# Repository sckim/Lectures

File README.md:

# 🎓 임베디드 및 디지털 시스템 설계 강의 자료 (Embedded & Digital System Design)

디지털 회로의 기초 원리부터 마이크로컨트롤러를 활용한 임베디드 프로그래밍까지, 제가 담당하는 교과목의 참고자료와 실습 예제를 체계적으로 정리한 저장소입니다.

This repository systematically organizes reference materials and practical examples for courses covering everything from fundamental digital circuit principles to embedded programming using microcontrollers.

---

## 📂 저장소 구조 (Repository Structure)

```text
.
├── 📗 Digital_Logics/      # 디지털 논리회로 및 시스템 설계 (Multisim, Proteus, Quartus, Simulink)
├── 📘 MicrochipStudio/     # 마이크로컨트롤러 실습 (AVR, ATmega328P, C/Assembly CPU 동작 이해)
├── 📙 RaspberryPi/         # 임베디드 시스템 (C, 다중 스레드, GPIO, BLE IoT, Simulink)
├── 🛰️ Adafruit feather.../ # nRF52840 기반 BLE 및 시리얼 통신 예제
├── 💻 VS2019/              # C 언어 기초 및 데이터 처리 실습
├── 🔌 Schematics/          # (이동) AD2 확장 키트 → Stm32NucleoF103RB 저장소 Schematics/AD2_extension
├── 📄 References.md        # 상세 학습 참고자료 및 교재 목록
└── 📄 LICENSE              # GNU GPL v3.0
```

---

## 🎓 담당 교과목 (Courses)

### 1️⃣ [디지털논리회로 (1학기)](https://docs.google.com/document/d/1-Nbt2U4_RxmWI0knJ9PB-1zacaE4BrXKlVAKuqOXOog/edit#heading=h.l577gc53wk1r)
*   **목표**: 논리 게이트, 조합 회로 및 순차 회로의 기초 이해
*   **실습 도구별 예제**:
    *   [Multisim 예제](/Digital_Logics/Multisim/) : 기본 게이트, 가산기, 비교기, 코드 변환기, 카운터
    *   [Proteus 예제](/Digital_Logics/Proteus/) : 래치/플립플롭, 쉬프트 레지스터(74LS164/165/194/195), 멀티플렉서, 디코더
    *   [Quartus 예제](/Digital_Logics/Quartus_schematics/) : FPGA 기반 스키매틱 설계 (조합회로 → 카운터 → 상태머신 → 디지털 시계)
    *   [Simulink 예제](/Digital_Logics/Simulink/) : 모델 기반 설계 (가산기, 플립플롭, 카운터, FSM, 자판기, 신호등)

### 2️⃣ [디지털시스템설계 (2학기)](https://docs.google.com/document/d/1w0CORrWaHI_NbjOskmIDs7_7yvQ0bz3ZSNFg1BX11ck/edit#heading=h.r1hokjytc0js)
*   **목표**: VHDL/Verilog를 이용한 하드웨어 설계 언어(HDL) 기초 및 응용
*   **주요 내용**: FPGA 보드(DE1-SoC 등) 활용 실습 및 복잡한 디지털 시스템 설계
*   **참고자료**: [References.md](References.md)의 *VHDL/Verilog 문법* 항목 (HDLBits, ModelSim Testbench 튜토리얼 등)

### 3️⃣ [마이크로컨트롤러 (1학기)](https://docs.google.com/document/d/1n3KUeXxMnC6K4D472Y-YwuZHPKo5krAnx2WdAsmD2wA/edit#heading=h.g1r703qpvjvj)
*   **목표**: AVR 아키텍처 이해 및 레지스터 기반 제어 학습
*   **실습 구성**:
    *   [C/Assembly 분석](/MicrochipStudio) : Disassembler와 디버거를 통한 CPU 동작 원리 이해 (`asmStart`, `asmBlink`, `add`, `return`, `while`)
    *   [C 언어 복습](/VS2019) : 임베디드 C 기초 다지기 (구조체, 파일 입출력, 디지털 필터, 시리얼 통신)
    *   [AD2 확장 키트](https://github.com/sckim/Stm32NucleoF103RB/tree/main/Schematics/AD2_extension) : Analog Discovery 2 연동 실습 보드 (KiCad, UNO/Nucleo/Feather 지원, I2C·PWM·SPI 레벨 시프터 온보드) — 2026-10 [Stm32NucleoF103RB](https://github.com/sckim/Stm32NucleoF103RB) 저장소로 이동

### 4️⃣ [임베디드시스템 (2학기)](https://docs.google.com/document/d/1DVsG6Le9iVnEqlcv0TA36XSPXYZ1sAhT7xt2vGAz96Q/edit)
*   **목표**: 고성능 프로세서 환경에서의 임베디드 운영체제 및 응용 프로그래밍
*   **주요 플랫폼**:
    *   교재 「라즈베리파이로 배우는 임베디드 시스템」 : 원고와 장별 예제 코드는 별도 저장소(`RaspberryPi_Textbook`, 비공개)에서 관리
    *   [Raspberry Pi 실습](/RaspberryPi) : Linux 기반 C 프로그래밍, 멀티스레드(Semaphore), 성능 측정
    *   [GPIO 제어](/RaspberryPi/Pigpio) : WiringPi / pigpio 라이브러리, RTC(DS1302), I2C LCD(PCF8574)
    *   [BLE IoT 프로젝트 (TS100)](/RaspberryPi/TS100/Gitbook) : BLE 체온계 → Raspberry Pi(Python) → AWS 클라우드 연동
    *   [nRF52840 예제](/Adafruit%20feather%20nRF52840%20express) : 저전력 블루투스(BLE) 통신 및 시리얼 통신

---

## 🛠️ 개발 환경 (Development Environment)

효과적인 학습을 위해 다음 도구들을 사용합니다:

*   **IDE**:
    *   [Microchip Studio](https://www.microchip.com/en-us/tools-resources/develop/microchip-studio) (AVR/ATmega 제어)
    *   [VS Code](https://code.visualstudio.com/) + [PlatformIO](https://platformio.org/) (추천 환경)
    *   Visual Studio 2019 (C 언어 기초)
*   **Simulation**:
    *   [Multisim](https://www.ni.com/ko-kr/support/downloads/software-products/download.multisim.html)
    *   [Proteus](https://www.labcenter.com/)
    *   [MATLAB/Simulink](https://www.mathworks.com/products/simulink.html)
*   **HDL/FPGA**: [Intel Quartus Prime](https://www.intel.co.kr/content/www/kr/ko/software/programmable/quartus-prime/overview.html)
*   **PCB 설계**: [KiCad](https://www.kicad.org/) ([KiCad 라이브러리 저장소](https://github.com/sckim/KiCAD))

---

## 🚀 시작하기 (Getting Started)

1.  **저장소 복제 (Clone)**:
    ```bash
    git clone https://github.com/sckim/Lectures.git
    ```
2.  **참고자료 확인**: [References.md](References.md)에서 교재 및 온라인 강의 링크를 확인하세요.
3.  **예제 실행**: 각 폴더의 README를 참고하여 프로젝트 파일을 해당 IDE에서 열어 실행합니다.
    *   Quartus 프로젝트는 `.qpf`, Microchip Studio는 `MicrochipStudio.atsln`, Visual Studio는 `VS2019.sln`을 엽니다.
    *   빌드 산출물(`db/`, `output_files/`, `Debug/` 등)은 저장소에 포함되지 않으므로 처음 열 때 한 번 컴파일하세요.

---

## ✉️ 문의 및 피드백 (Contact & Feedback)

학습 중 궁금한 점이나 보완이 필요한 내용은 언제든지 아래로 연락 바랍니다:
*   **이메일**: sckim@hknu.ac.kr
*   **GitHub Issues**: 오류 제보나 기능 제안은 Issue를 이용해 주세요.

---

## ⚖️ 라이선스 (License)

이 저장소의 코드는 [GNU General Public License v3.0](LICENSE)을 따릅니다.

---
*지속적으로 업데이트 중입니다. 학생 여러분의 학습에 도움이 되길 바랍니다!*

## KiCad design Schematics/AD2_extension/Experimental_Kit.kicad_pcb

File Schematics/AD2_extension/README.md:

# 🔌 AD2 확장 키트 (Analog Discovery 2 Extension Kit)

Analog Discovery 2(AD2)와 마이크로컨트롤러 보드를 함께 꽂아 실습하는 확장 보드의 KiCad 프로젝트입니다.
Arduino UNO R3 호환 헤더, STM32 Nucleo Morpho 헤더(CN7/CN10), Adafruit Feather 소켓을 지원하며, 5V 주변장치(LCD, PWM)와 3.3V 주변장치(SPI)를 위한 레벨 시프터가 보드에 실장되어 있습니다.

---

## 📂 파일 구성 (Files)

| 파일 | 내용 |
| :--- | :--- |
| `Experimental_Kit.kicad_pro` | KiCad 프로젝트 파일 (이 파일을 여세요) |
| `Experimental_Kit.kicad_sch` | 회로도 |
| `Experimental_Kit.kicad_pcb` | PCB (2층, 배선 및 GND 동박 완료) |
| `AD2_extension.kicad_sym`, `sym-lib-table` | 프로젝트 심볼 라이브러리 (TXU0304PW) |
| `AD2_extension.pretty/`, `fp-lib-table` | 프로젝트 풋프린트 라이브러리 (UNO 실드 헤더, 2×19 미러 소켓) |

---

## 🧩 커넥터 (Connectors)

| 레퍼런스 | 이름 | 용도 |
| :--- | :--- | :--- |
| A1 | Arduino_UNO_R3 | Arduino UNO R3 호환 헤더 |
| J11 / J13 | CN7 / CN10 | STM32 Nucleo Morpho 헤더 |
| MS1 | Feather | Adafruit Feather 소켓 |
| J10 | AD2 | Analog Discovery 2 연결 |
| J2 | Keypad | 키패드 (전원 IOREF) |
| J3 | LCD | I2C LCD (5V, 레벨 시프트된 SDA/SCL) |
| J5 / J6 | PWM | 5V PWM 출력 (DIO3 / DIO5) |
| J14 | SPI | 3.3V SPI 장치 |
| J12 | IOREF | IOREF–3V3 연결 헤더 (아래 참고) |
| J7 / J9 | AREF / W1 | 아날로그 기준 전압 / AD2 파형 발생기 |

---

## 🔁 온보드 레벨 시프터 (On-board Level Shifters)

이전 버전은 BSS138 레벨 시프터 모듈을 헤더(J2/J4)에 꽂아 사용했으나, 현재는 보드에 직접 실장했습니다.
호스트 쪽 전압은 **IOREF**를 기준으로 하므로 5V 보드(UNO)와 3.3V 보드(Nucleo, Feather) 모두에서 규격에 맞는 신호 레벨이 나옵니다.

| 신호 | 회로 | 방향 |
| :--- | :--- | :--- |
| SDA, SCL → LCD | 2N7002 MOSFET (Q1, Q2), 호스트 쪽 풀업 4.7kΩ, 5V 쪽 풀업 10kΩ | 양방향 |
| DIO3, DIO5 → PWM | 2N7002 MOSFET (Q3, Q4), 풀업 10kΩ | IOREF → 5V |
| DIO13/11/10 → SCK/MOSI/CS | TXU0304 (U1), VCCA = IOREF, VCCB = 3.3V | 호스트 → 장치 |
| MISO ← DIO12 | TXU0304 (U1) | 장치 → 호스트 |

> ⚠️ **Feather 사용 시**: Feather에는 IOREF 핀이 없으므로 **J12(IOREF)에 점퍼를 꽂아** IOREF를 3.3V에 연결해야 레벨 시프터가 동작합니다. UNO/Nucleo 사용 시에는 점퍼를 빼 두세요.

---

## 🛠️ 여는 방법 (How to Open)

1. [KiCad](https://www.kicad.org/) 최신 버전을 설치합니다.
2. `Experimental_Kit.kicad_pro`를 엽니다. 프로젝트 라이브러리(`sym-lib-table`, `fp-lib-table`)는 자동으로 로드됩니다.
3. 추가 라이브러리는 [KiCad 라이브러리 저장소](https://github.com/sckim/KiCAD)를 참고하세요.

---

*[메인 README.md로 돌아가기](../../README.md)*

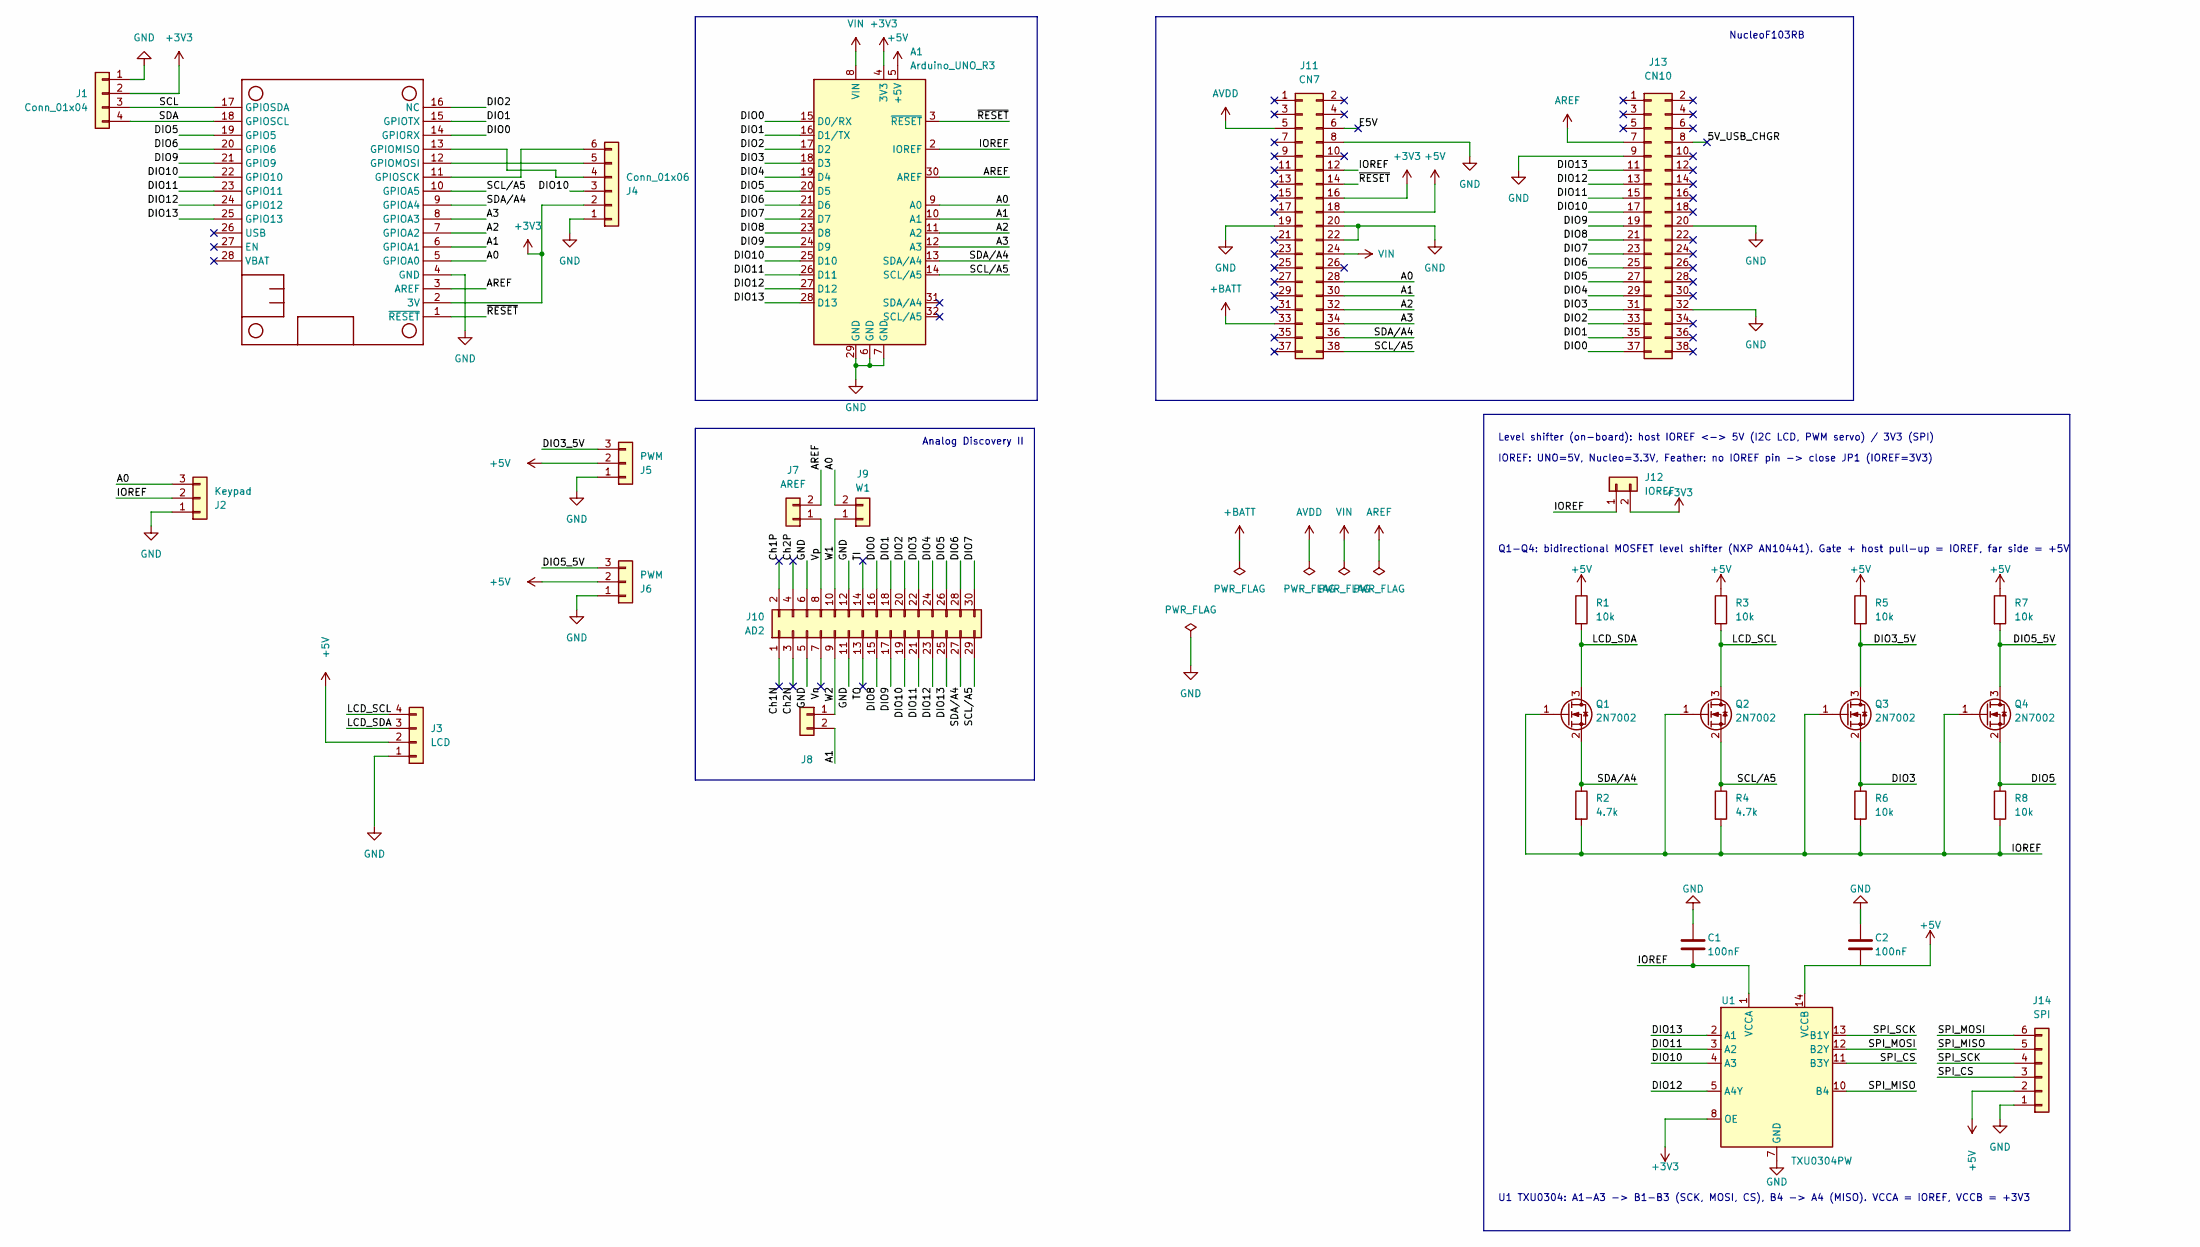
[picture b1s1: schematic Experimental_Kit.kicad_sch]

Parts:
A1: Arduino_UNO_R3; Arduino_UNO_R3_ShieldHeaders
C1, C2: 100nF; C_0805_2012Metric_Pad1.18x1.45mm_HandSolder
J1: Conn_01x04; PinHeader_1x04_P2.54mm_Vertical
J2: Keypad; PinHeader_1x03_P2.54mm_Vertical
J3: LCD; PinHeader_1x04_P2.54mm_Vertical
J4: Conn_01x06
J5, J6: PWM; PinHeader_1x03_P2.54mm_Vertical
J7: AREF; PinHeader_1x02_P2.54mm_Vertical
J8: Conn_01x02; PinHeader_1x02_P2.54mm_Vertical
J9: W1; PinHeader_1x02_P2.54mm_Vertical
J10: AD2; PinSocket_2x15_P2.54mm_Horizontal
J11: CN7; PinSocket_2x19_P2.54mm_Vertical_Mirrored
J12: IOREF; PinHeader_1x02_P2.54mm_Vertical
J13: CN10; PinSocket_2x19_P2.54mm_Vertical_Mirrored
J14: SPI; PinHeader_1x06_P2.54mm_Vertical
MS1: FEATHERWING_NODIM
Q1, Q2, Q3, Q4: 2N7002; SOT-23
R1, R3, R5, R6, R7, R8: 10k; R_0805_2012Metric_Pad1.20x1.40mm_HandSolder
R2, R4: 4.7k; R_0805_2012Metric_Pad1.20x1.40mm_HandSolder
U1: TXU0304PW; TSSOP-14_4.4x5mm_P0.65mm

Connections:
+3V3: A1.4 (3V3), J1.2, J4.2, J11.16, J12.2, MS1.2 (3V), U1.8 (OE)
+5V: A1.5 (+5V), J3.2, J5.2, J6.2, J11.18, J14.2, R1.1, R3.1, R5.1, R7.1, U1.14 (VCCB)
+BATT: J11.33
/5V_USB_CHGR: J13.8
/A0: A1.9 (A0), J2.3, J9.2, J11.28, MS1.5 (GPIOA0)
/A1: A1.10 (A1), J8.2, J11.30, MS1.6 (GPIOA1)
/A2: A1.11 (A2), J11.32, MS1.7 (GPIOA2)
/A3: A1.12 (A3), J11.34, MS1.8 (GPIOA3)
/Ch1N: J10.1
/Ch1P: J10.2
/Ch2N: J10.3
/Ch2P: J10.4
/DIO0: A1.15 (D0/RX), J10.16, J13.37, MS1.14 (GPIORX)
/DIO1: A1.16 (D1/TX), J10.18, J13.35, MS1.15 (GPIOTX)
/DIO2: A1.17 (D2), J10.20, J13.33, MS1.16 (NC)
/DIO3: A1.18 (D3), J10.22, J13.31, Q3.2 (S), R6.1
/DIO3_5V: J5.3, Q3.3 (D), R5.2
/DIO4: A1.19 (D4), J10.24, J13.29
/DIO5: A1.20 (D5), J10.26, J13.27, MS1.19 (GPIO5), Q4.2 (S), R8.1
/DIO5_5V: J6.3, Q4.3 (D), R7.2
/DIO6: A1.21 (D6), J10.28, J13.25, MS1.20 (GPIO6)
/DIO7: A1.22 (D7), J10.30, J13.23
/DIO8: A1.23 (D8), J10.15, J13.21
/DIO9: A1.24 (D9), J10.17, J13.19, MS1.21 (GPIO9)
/DIO10: A1.25 (D10), J4.3, J10.19, J13.17, MS1.22 (GPIO10), U1.4 (A3)
/DIO11: A1.26 (D11), J10.21, J13.15, MS1.23 (GPIO11), U1.3 (A2)
/DIO12: A1.27 (D12), J10.23, J13.13, MS1.24 (GPIO12), U1.5 (A4Y)
/DIO13: A1.28 (D13), J10.25, J13.11, MS1.25 (GPIO13), U1.2 (A1)
/E5V: J11.6
/IOREF: A1.2 (IOREF), C1.2, J2.2, J11.12, J12.1, Q1.1 (G), Q2.1 (G), Q3.1 (G), Q4.1 (G), R2.2, R4.2, R6.2, R8.2, U1.1 (VCCA)
/LCD_SCL: J3.4, Q2.3 (D), R3.2
/LCD_SDA: J3.3, Q1.3 (D), R1.2
/SCL: J1.3, MS1.17 (GPIOSDA)
/SCL/A5: A1.14 (SCL/A5), J10.29, J11.38, MS1.10 (GPIOA5), Q2.2 (S), R4.1
/SDA: J1.4, MS1.18 (GPIOSCL)
/SDA/A4: A1.13 (SDA/A4), J10.27, J11.36, MS1.9 (GPIOA4), Q1.2 (S), R2.1
/SPI_CS: J14.3, U1.11 (B3Y)
/SPI_MISO: J14.5, U1.10 (B4)
/SPI_MOSI: J14.6, U1.12 (B2Y)
/SPI_SCK: J14.4, U1.13 (B1Y)
/TI: J10.14
/TO: J10.13
/Vn: J10.7
/Vp: J7.1, J10.8
/W1: J9.1, J10.10
/W2: J8.1, J10.9
/~RESET: A1.3 (~RESET), J11.14, MS1.1 (~RESET)
AREF: A1.30 (AREF), J7.2, J13.7, MS1.3 (AREF)
AVDD: J11.5
GND: A1.6 (GND), A1.7 (GND), A1.29 (GND), C1.1, C2.1, J1.1, J2.1, J3.1, J4.1, J5.1, J6.1, J10.5, J10.6, J10.11, J10.12, J11.8, J11.19, J11.20, J11.22, J13.9, J13.20, J13.32, J14.1, MS1.4 (GND), U1.7 (GND)
unnamed: J4.4, MS1.13 (GPIOMISO)
unnamed: J4.5, MS1.12 (GPIOMOSI)
unnamed: J4.6, MS1.11 (GPIOSCK)
VIN: A1.8 (VIN), J11.24

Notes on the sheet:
Level shifter (on-board): host IOREF <-> 5V (I2C LCD, PWM servo) / 3V3 (SPI)
IOREF: UNO=5V, Nucleo=3.3V, Feather: no IOREF pin -> close JP1 (IOREF=3V3)
Q1-Q4: bidirectional MOSFET level shifter (NXP AN10441). Gate + host pull-up = IOREF, far side = +5V
NucleoF103RB
Analog Discovery II
U1 TXU0304: A1-A3 -> B1-B3 (SCK, MOSI, CS), B4 -> A4 (MISO). VCCA = IOREF, VCCB = +3V3

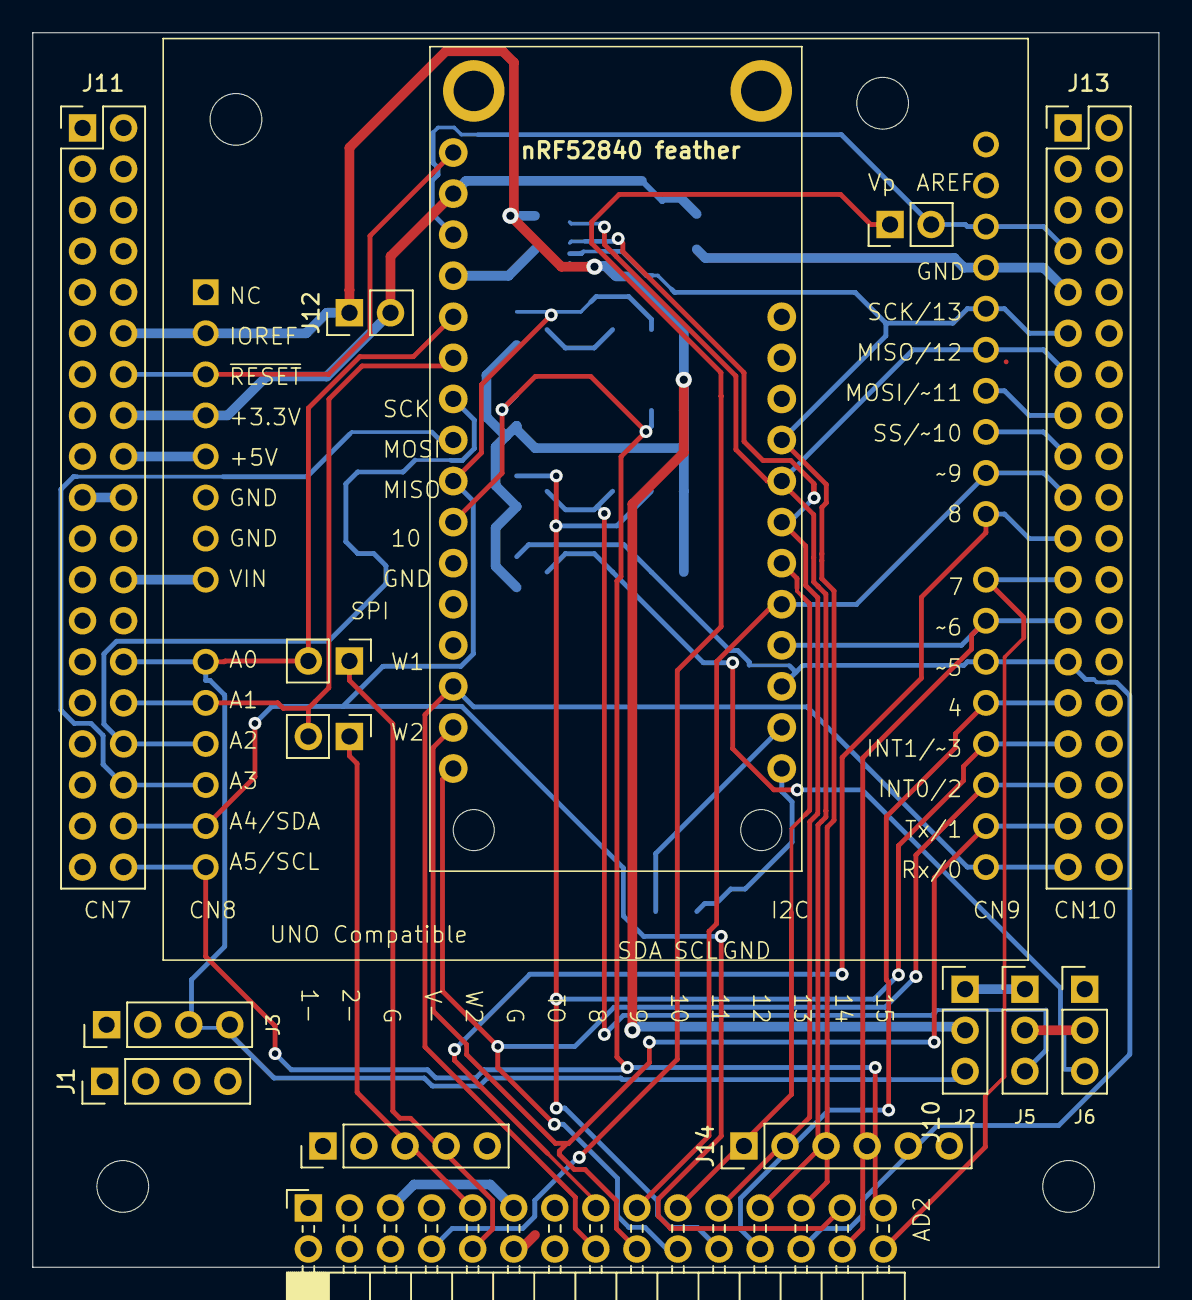
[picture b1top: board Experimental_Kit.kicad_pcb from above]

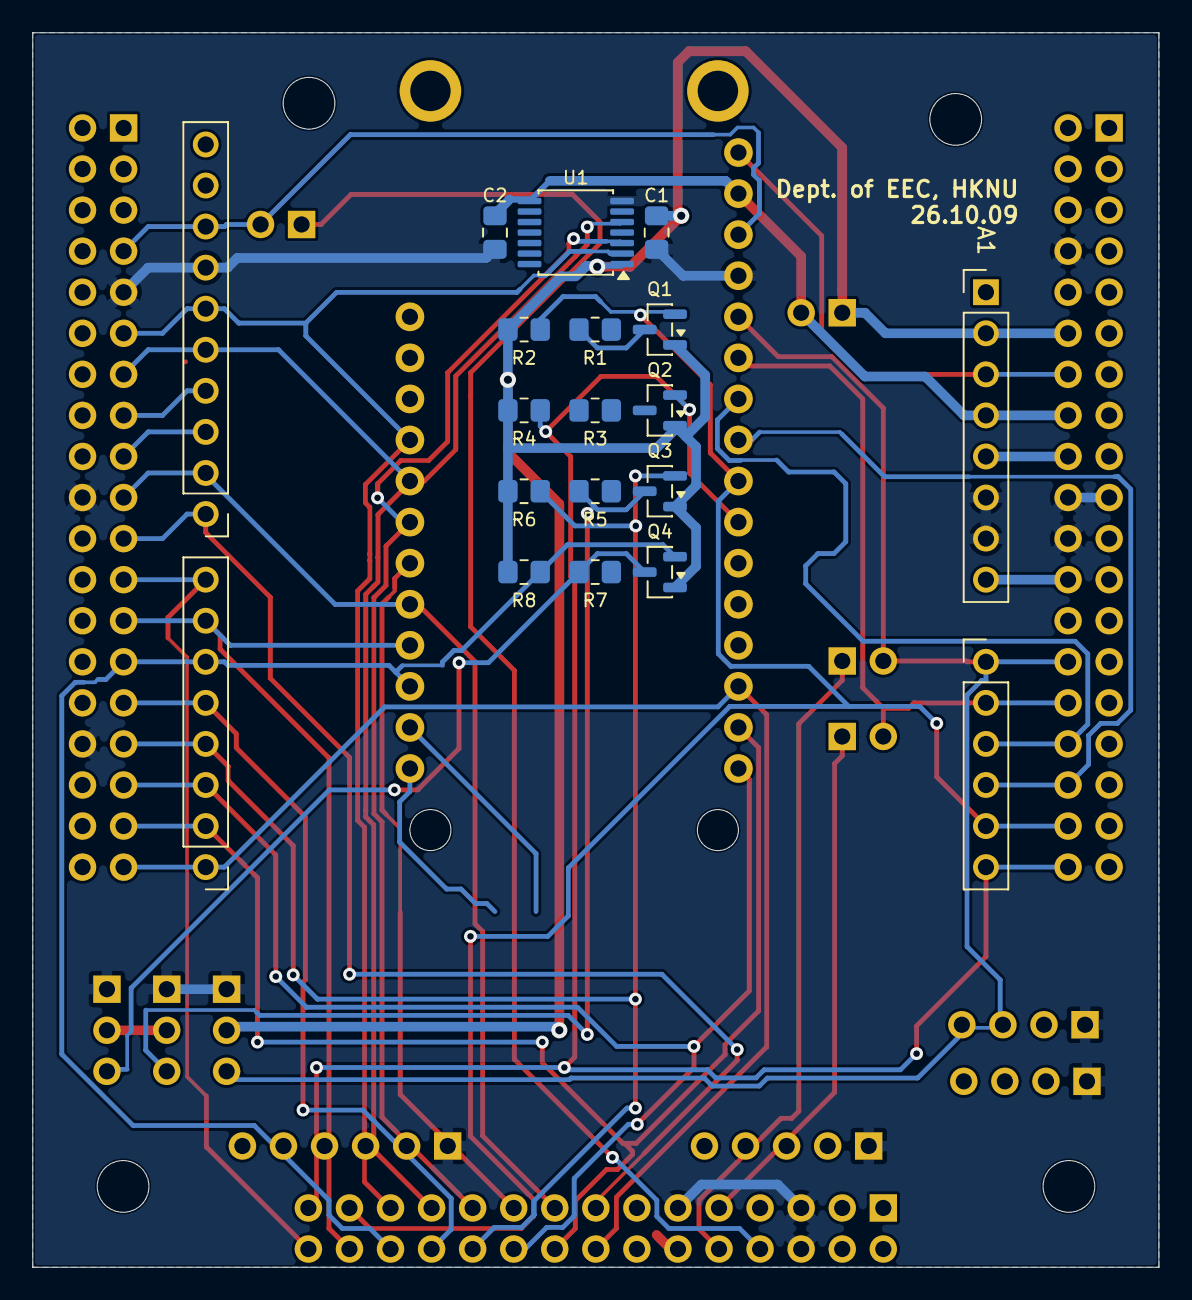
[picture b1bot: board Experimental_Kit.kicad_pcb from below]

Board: 2 copper layers, 69.7 x 76.4 mm, 35 parts (16 on the bottom side), 42 nets.

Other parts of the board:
H1, H2, H3, H4: MountingHole_3.2mm_M3

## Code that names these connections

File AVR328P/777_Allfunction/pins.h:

#ifndef Pins_h
#define Pins_h

#include <avr/io.h>
#include <avr/pgmspace.h>

#define NOT_A_PIN 0
#define NOT_A_PORT 0

#define HIGH 0x1
#define LOW  0x0

#define INPUT 0x0
#define OUTPUT 0x1
#define INPUT_PULLUP 0x2


#define NUM_DIGITAL_PINS            20
#define NUM_ANALOG_INPUTS           6
#define analogInputToDigitalPin(p)  ((p < 6) ? (p) + 14 : -1)

#define digitalPinHasPWM(p)         ((p) == 3 || (p) == 5 || (p) == 6 || (p) == 9 || (p) == 10 || (p) == 11)

#define PIN_SPI_SS    (10)
#define PIN_SPI_MOSI  (11)
#define PIN_SPI_MISO  (12)
#define PIN_SPI_SCK   (13)

static const uint8_t SS   = PIN_SPI_SS;
static const uint8_t MOSI = PIN_SPI_MOSI;
static const uint8_t MISO = PIN_SPI_MISO;
static const uint8_t SCK  = PIN_SPI_SCK;

#define PIN_WIRE_SDA        (18)
#define PIN_WIRE_SCL        (19)

static const uint8_t SDA = PIN_WIRE_SDA;
static const uint8_t SCL = PIN_WIRE_SCL;

#define LED_BUILTIN 13

#define PB 2
#define PC 3
#define PD 4

#define digitalPinToPCICR(p)    (((p) >= 0 && (p) <= 21) ? (&PCICR) : ((uint8_t *)0))
#define digitalPinToPCICRbit(p) (((p) <= 7) ? 2 : (((p) <= 13) ? 0 : 1))
#define digitalPinToPCMSK(p)    (((p) <= 7) ? (&PCMSK2) : (((p) <= 13) ? (&PCMSK0) : (((p) <= 21) ? (&PCMSK1) : ((uint8_t *)0))))
#define digitalPinToPCMSKbit(p) (((p) <= 7) ? (p) : (((p) <= 13) ? ((p) - 8) : ((p) - 14)))

#define digitalPinToInterrupt(p)  ((p) == 2 ? 0 : ((p) == 3 ? 1 : NOT_AN_INTERRUPT))

#define digitalPinToPort(P) ( pgm_read_byte( digital_pin_to_port_PGM + (P) ) )
#define digitalPinToBitMask(P) ( pgm_read_byte( digital_pin_to_bit_mask_PGM + (P) ) )
#define digitalPinToTimer(P) ( pgm_read_byte( digital_pin_to_timer_PGM + (P) ) )
#define analogInPinToBit(P) (P)
#define portOutputRegister(P) ( (volatile uint8_t *)( pgm_read_word( port_to_output_PGM + (P))) )
#define portInputRegister(P) ( (volatile uint8_t *)( pgm_read_word( port_to_input_PGM + (P))) )
#define portModeRegister(P) ( (volatile uint8_t *)( pgm_read_word( port_to_mode_PGM + (P))) )

#endif

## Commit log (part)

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2024-05-24 Add examples
2024-05-24 Move references.md
2024-05-24 Add english introduction
2024-05-24 Edit
2024-05-24 Add readme.md and .gitignore
2024-05-24 Update 반, 전가산기
2024-05-24 delete
2024-05-30 Add #define _CRT_SECURE_NO_WARNINGS
2024-05-31 0531 15:04
2024-05-31 24/05/31 15:17
2024-05-31 24/05/31 15:30
2024-05-31 test
2024-05-31 24/05/31 20:33
2024-05-31 24/05/31 21:33
    ~ 레지스터 까지 완료
    남은것 : n-비트 카운터 ~
    1. README.md 에서 디렉토리 설정 가능하도록 파일명 수정하기
    띄어쓰기 '_'로 바꾸기
    2. 강의자료 기준 4.3 비동기식 카운터 부터
    동기 / 비동기
2024-05-31 24/05/31 21:37 ~ 레지스터 까지 완료
    남은것 : n-비트 카운터 ~
    1. README.md 에서 디렉토리 설정 가능하도록 파일명 수정하기
    띄어쓰기 '_'로 바꾸기
    2. 강의자료 기준 4.3 비동기식 카운터 부터
    동기 / 비동기
    순차회로 해석/ 순차회로 설계
2024-05-31 Multisim 24/05/31 22:22
    남은것
    1.multisim 설치
    2.파일별 사진 캡쳐
    3.디렉토리로 파일 링크삽입 가능하도록 파일명 수정하기
    띄어쓰기 '_'로
    가능하면 영문명
2024-05-31 Proteus 24/05/31 22:57
    남은것
    1. 디렉토리로 링크설정 가능하도록 파일명 변경
    띄어쓰기 '_'로 변경
    가능하면 영문 파일명
    2. README에 파일링크 추가
    3. 사진 캡쳐 추가하기
2024-06-01 Proteus 24/06/02 02:24
    폴더에 들어있던 모든 Proteus 파일 적용완료
    1. 파일명 강의자료 기준 번호로 수정, 영문명
    2. 조합논리회로 실험 강의자료에 해당하는 파일은 별도 폴더에
    Proteus/combinational_logic_circuit/
    KIM DONGYEON
2024-06-02 폴더 생성
    -번호별 폴더 생성
    -16,17 순서 변경
    -~12까지 사진 캡쳐 완료
2024-06-02 폴더 생성, 사진 캡쳐 완료
    -18번까지 폴더 생성, 사진 캡쳐 완료
2024-06-02 이미지 올리기 테스트
2024-06-02 사진 추가 완료
    -번호별 사진 추가 완료
2024-06-02 6/3 12:05
    -폴더 생성 완료
    -16,17 순서 변경
    -폴더 안 ,번호별 사진 추가 완료
    (남은것)
    -제목 클릭 -> 시뮬레이션 ms14 파일
    -![_vwf_simulation]() 이게 의미하는바 알아보기 + 추가
2024-06-02 Multisim 24/06/03 01:04
    폴더에 들어있던 모든 Multisim 파일 적용 완료
    1. 파일명 강의자료 기준 번호로 수정, 영문명
    2. 순차논리회로 실험 강의자료에 해당하는 파일은 별도 폴더에
    Multisim/sequential_logic_circuits/
    KIM DONGYEON
2024-06-07 Quartus 24/06/08 00:27 순차논리회로 4.1까지 완료
2024-06-10 Update QM
2024-06-13 quartus 24/06/14 00:32 파일명변경완료
    남은것
    4.1부터 회로도, 시뮬레이션 파일 추가하기
2024-06-20 Quartus 24/06/20 17:36 완
2024-06-20 Proteus 24/06/20 18:36
    사진파일 흰 배경으로 교체
2024-06-20 Proteus 24/06/20 18:39
    사진 배경색 수정
2024-06-29 Update References.md
    https://vhdlwhiz.com/
2024-06-30 Add vhdlwhiz.com examples
2024-07-14 Add tri_state
2024-09-25 Add asmStart & asmBlink examples
2025-04-24 Add Analog Engineer's Pocket Ref
2025-11-09 Add simulink files
2025-11-09 move simulink files to Logics
2025-11-09 Add README with Simulink examples
2025-11-10 Add missing files
2025-11-12 Add hdl coder
2025-11-26 Update quartus and vhdl files
2025-11-26 Update VHDL
2025-11-28 Update files
2025-11-28 Check digitalClock
2025-11-28 Update FA
2025-12-01 Add pigpio examples
2025-12-01 Add wiringPi, pigpio
2025-12-01 Add TS100
2025-12-01 Add wiringPi
2025-12-01 Add sof, pof
2025-12-02 Add files
2025-12-03 revise lcd_pcf8574.c
2025-12-11 change file
2026-03-11 Edit
    - Sampling rate
    - Pulse generator
2026-04-10 Update some files
2026-06-06 git commit -m "Fix: .gitignore 적용 및 Debug/ build/ WiringPi-master/ Wokwi/ Pigpio-master/ 제외
2026-06-28 Update references for VHDL/Verilog syntax
